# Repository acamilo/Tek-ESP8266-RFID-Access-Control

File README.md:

# Tek-ESP8266-RFID-Access-Control

## Requirements ##
* Accept [Wiegand](https://en.wikipedia.org/wiki/Wiegand_interface) data from a rfid reader
* Power everything off of a 12v wall wart.
* Query a database over WiFi with card data.
* Controll Relays, Lights, Door latches

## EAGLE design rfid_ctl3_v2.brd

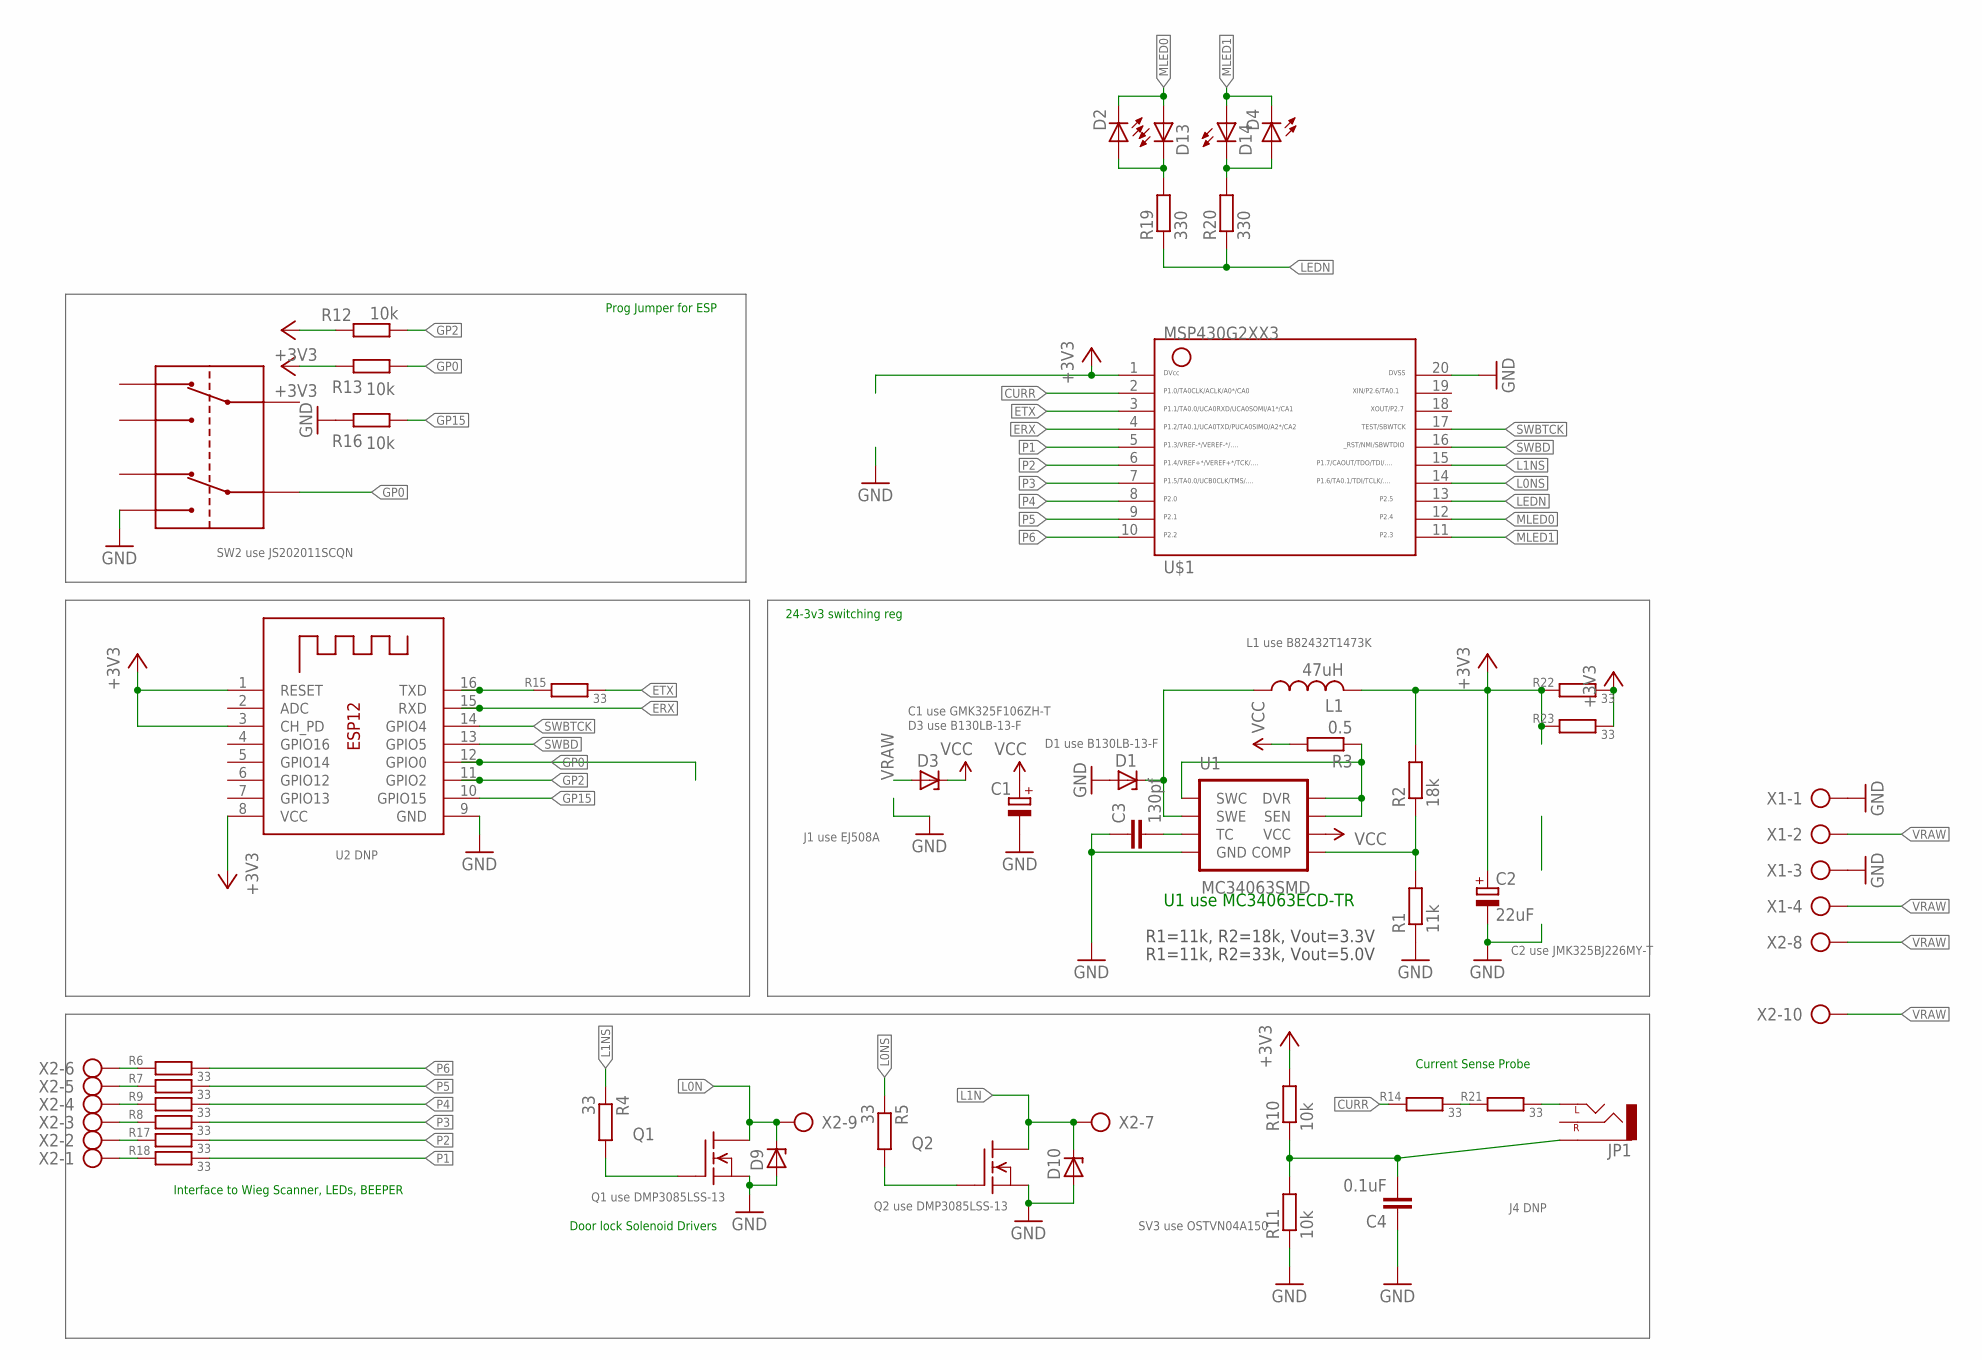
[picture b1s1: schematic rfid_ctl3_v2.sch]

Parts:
C1: CPOL-EUE2.5-7; E2,5-7
C2: 22uF; E2,5-7
C3: 130pf; C1206
C4: 0.1uF; C1206
D1, D3, D9, D10: ZENER-DIODESMB; SMB
D2, D4, D13, D14: LED5MM
JP1: AUDIO-JACKSMD2; AUDIO-JACK-3.5MM-SMD
L1: 47uH; L1812
Q1, Q2: FDS5680; SO-8
R1: 11k; R1206
R2: 18k; R1206
R3: 0.5; R1206
R4, R5, R6, R7, R8, R9, R14, R15, R17, R18, R21: 33; R1206
R10, R11, R12, R13, R16: 10k; R1206
R19, R20: 330; R1206
R22, R23: 33; R6332
SW2: L202011MS02Q; SMT
U1: MC34063SMD; SO08
U2: ESP-12
U$1: G2XX3---N20; N20
X1: AK300/4
X2: AK300/10

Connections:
+3V3: C2.+, L1.2, R2.2, R10.2, R12.2, R13.2, R22.1, R22.2, R23.1, R23.2, U2.1 (RESET), U2.3 (CH_PD), U2.8 (VCC), U$1.1
CURR: R14.1, U$1.2
ERX: U2.15 (RXD), U$1.4
ETX: R15.2, U$1.3
GND: C1.-, C2.-, C3.1, C4.1, D1.A, D9.A, D10.A, Q1.1 (S), Q1.2 (S), Q1.3 (S), Q2.1 (S), Q2.2 (S), Q2.3 (S), R1.1, R11.1, R16.2, SW2.B1, U1.4 (GND), U2.9 (GND), U$1.20, X1.1, X1.3
GP0: R13.1, SW2.B, U2.12 (GPIO0)
GP2: R12.1, U2.11 (GPIO2)
GP15: R16.1, U2.10 (GPIO15)
L0N: D9.C, Q1.5 (D), Q1.6 (D), Q1.7 (D), Q1.8 (D), X2.9
L0NS: R5.1, U$1.14
L1N: D10.C, Q2.5 (D), Q2.6 (D), Q2.7 (D), Q2.8 (D), X2.7
L1NS: R4.1, U$1.15
LEDN: R19.1, R20.1, U$1.13
MLED0: D2.K (C), D13.A, U$1.12
MLED1: D4.K (C), D14.A, U$1.11
unnamed: Q1.4 (G), R4.2
unnamed: C3.2, U1.3 (TC)
unnamed: D1.C, L1.1, U1.2 (SWE)
unnamed: Q2.4 (G), R5.2
unnamed: R1.2, R2.1, U1.5 (COMP)
unnamed: R3.1, U1.1 (SWC), U1.7 (SEN), U1.8 (DVR)
unnamed: R14.2, R21.1
unnamed: R6.1, X2.6
unnamed: R7.1, X2.5
unnamed: R8.1, X2.4
unnamed: R9.1, X2.3
unnamed: C4.2, JP1.SLEEVE, R10.1, R11.2
unnamed: JP1.TIP (LEFT), R21.2
unnamed: D2.A, D13.K (C), R19.2
unnamed: D4.A, D14.K (C), R20.2
unnamed: R17.1, X2.2
unnamed: R18.1, X2.1
unnamed: R15.1, U2.16 (TXD)
P1: R18.2, U$1.5
P2: R17.2, U$1.6
P3: R9.2, U$1.7
P4: R8.2, U$1.8
P5: R7.2, U$1.9
P6: R6.2, U$1.10
SWBD: U2.13 (GPIO5), U$1.16
SWBTCK: U2.14 (GPIO4), U$1.17
VCC: C1.+, D3.C, R3.2, U1.6 (VCC)
VRAW: D3.A, X1.2, X1.4, X2.8, X2.10

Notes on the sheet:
R1=11k, R2=18k, Vout=3.3V
R1=11k, R2=33k, Vout=5.0V
Q1 use DMP3085LSS-13
Q2 use DMP3085LSS-13
C2 use JMK325BJ226MY-T
C1 use GMK325F106ZH-T
D3 use B130LB-13-F
D1 use B130LB-13-F
L1 use B82432T1473K
J1 use EJ508A
SV3 use OSTVN04A150
SW2 use JS202011SCQN
J4 DNP
U2 DNP
U1 use MC34063ECD-TR
Prog Jumper for ESP
24-3v3 switching reg
Interface to Wieg Scanner, LEDs, BEEPER
Door lock Solenoid Drivers
Current Sense Probe

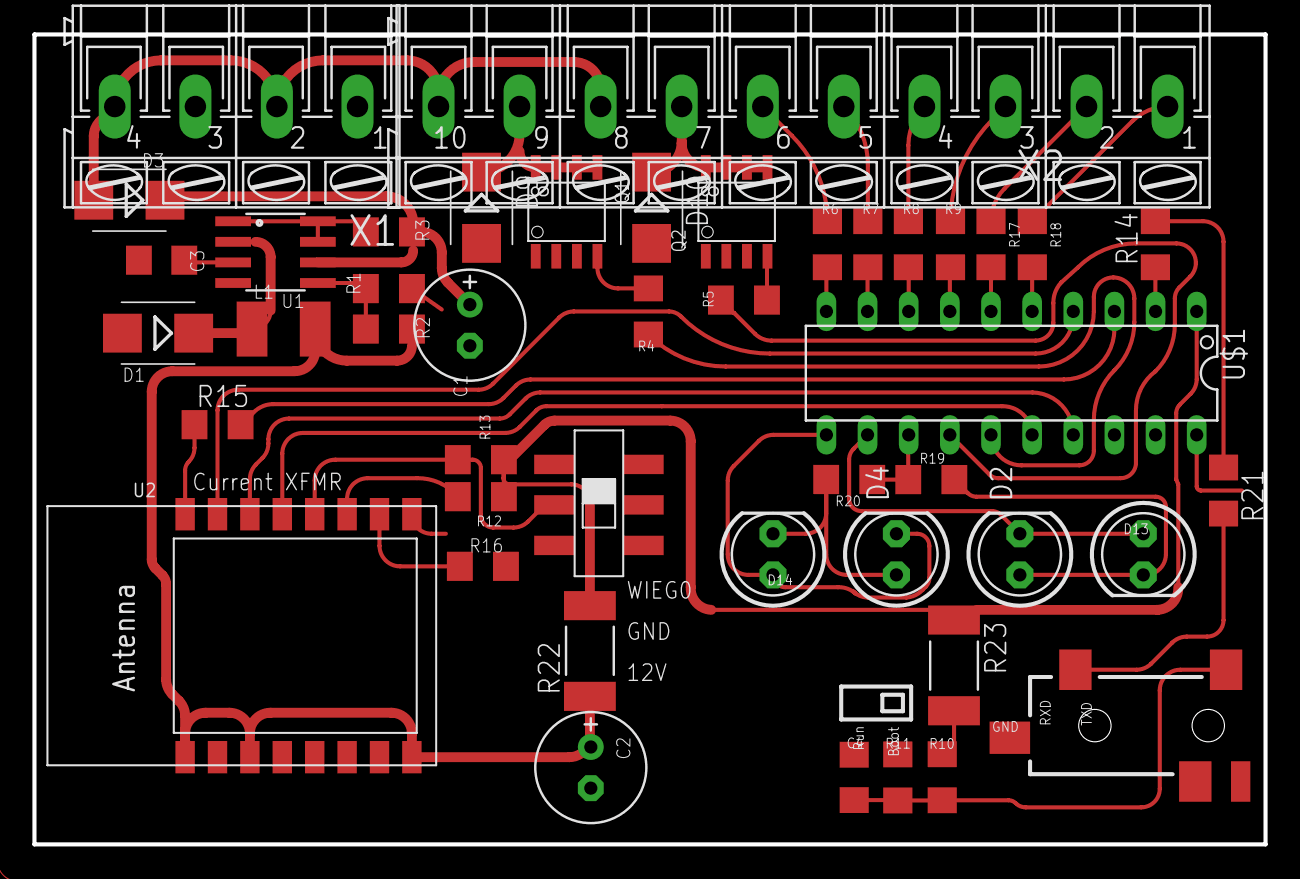
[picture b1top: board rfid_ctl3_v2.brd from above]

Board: 2 copper layers, 76.0 x 50.0 mm, 45 parts (0 on the bottom side), 43 nets.

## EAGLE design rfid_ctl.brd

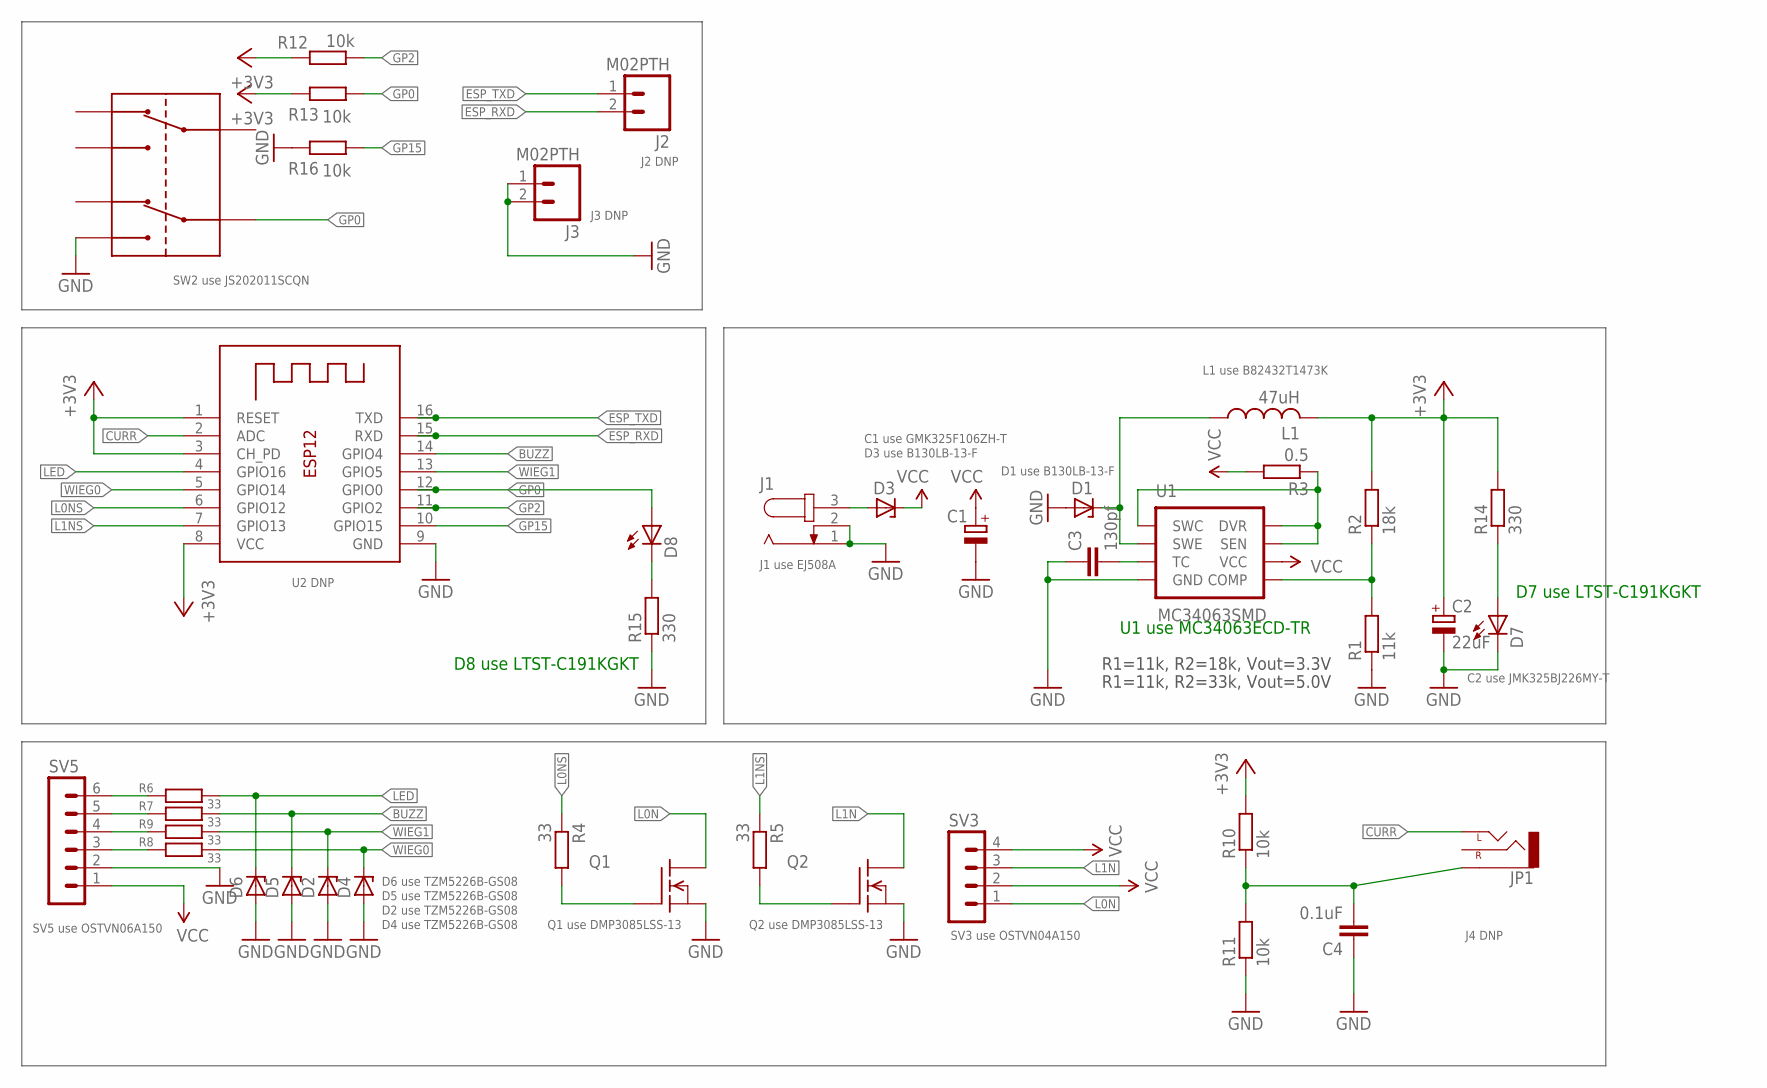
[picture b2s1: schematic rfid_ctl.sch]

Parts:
C1: CPOL-EUB/3528-21R; B/3528-21R
C2: 22uF; B/3528-21R
C3: 130pf; C0603
C4: 0.1uF; C0603
D1, D3: ZENER-DIODESMB; SMB
D2, D4, D5, D6: ZENER-DIODESOD80C; SOD80C
D7, D8: LEDCHIP-LED0603; CHIP-LED0603
J1: JACK-PLUG0; SPC4077
J2, J3: M02PTH; 1X02
JP1: AUDIO-JACKSMD2; AUDIO-JACK-3.5MM-SMD
L1: 47uH; L1812
Q1, Q2: FDS5680; SO-8
R1: 11k; R0603
R2: 18k; R0603
R3: 0.5; R0603
R4, R5, R6, R7, R8, R9: 33; R0603
R10, R11, R12, R13, R16: 10k; R0603
R14, R15: 330; R0603
SV3: MA04-1
SV5: MA06-1
SW2: L202011MS02Q; SMT
U1: MC34063SMD; SO08
U2: ESP-12

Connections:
+3V3: C2.+, L1.2, R2.2, R10.2, R12.2, R13.2, R14.2, U2.1 (RESET), U2.3 (CH_PD), U2.8 (VCC)
BUZZ: D5.C, R7.2, U2.14 (GPIO4)
CURR: JP1.TIP (LEFT), U2.2 (ADC)
ESP_RXD: J2.2, U2.15 (RXD)
ESP_TXD: J2.1, U2.16 (TXD)
GND: C1.-, C2.-, C3.1, C4.1, D1.A, D2.A, D4.A, D5.A, D6.A, D7.C, J1.1, J1.2, J3.1, J3.2, Q1.1 (S), Q1.2 (S), Q1.3 (S), Q2.1 (S), Q2.2 (S), Q2.3 (S), R1.1, R11.1, R15.1, R16.2, SV5.2, SW2.B1, U1.4 (GND), U2.9 (GND)
GP0: D8.A, R13.1, SW2.B, U2.12 (GPIO0)
GP2: R12.1, U2.11 (GPIO2)
GP15: R16.1, U2.10 (GPIO15)
L0N: Q1.5 (D), Q1.6 (D), Q1.7 (D), Q1.8 (D), SV3.1
L0NS: R4.1, U2.6 (GPIO12)
L1N: Q2.5 (D), Q2.6 (D), Q2.7 (D), Q2.8 (D), SV3.3
L1NS: R5.1, U2.7 (GPIO13)
LED: D6.C, R6.2, U2.4 (GPIO16)
unnamed: Q1.4 (G), R4.2
unnamed: C3.2, U1.3 (TC)
unnamed: D1.C, L1.1, U1.2 (SWE)
unnamed: Q2.4 (G), R5.2
unnamed: R1.2, R2.1, U1.5 (COMP)
unnamed: R3.1, U1.1 (SWC), U1.7 (SEN), U1.8 (DVR)
unnamed: D3.A, J1.3
unnamed: R6.1, SV5.6
unnamed: R7.1, SV5.5
unnamed: R8.1, SV5.4
unnamed: R9.1, SV5.3
unnamed: C4.2, JP1.SLEEVE, R10.1, R11.2
unnamed: D7.A, R14.1
unnamed: D8.C, R15.2
VCC: C1.+, D3.C, R3.2, SV3.2, SV3.4, SV5.1, U1.6 (VCC)
WIEG0: D4.C, R9.2, U2.5 (GPIO14)
WIEG1: D2.C, R8.2, U2.13 (GPIO5)

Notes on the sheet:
R1=11k, R2=18k, Vout=3.3V
R1=11k, R2=33k, Vout=5.0V
Q1 use DMP3085LSS-13
Q2 use DMP3085LSS-13
D6 use TZM5226B-GS08
D5 use TZM5226B-GS08
D2 use TZM5226B-GS08
D4 use TZM5226B-GS08
C2 use JMK325BJ226MY-T
C1 use GMK325F106ZH-T
D3 use B130LB-13-F
D1 use B130LB-13-F
L1 use B82432T1473K
J1 use EJ508A
SV5 use OSTVN06A150
SV3 use OSTVN04A150
SW2 use JS202011SCQN
J2 DNP
J3 DNP
J4 DNP
U2 DNP
U1 use MC34063ECD-TR
D7 use LTST-C191KGKT
D8 use LTST-C191KGKT

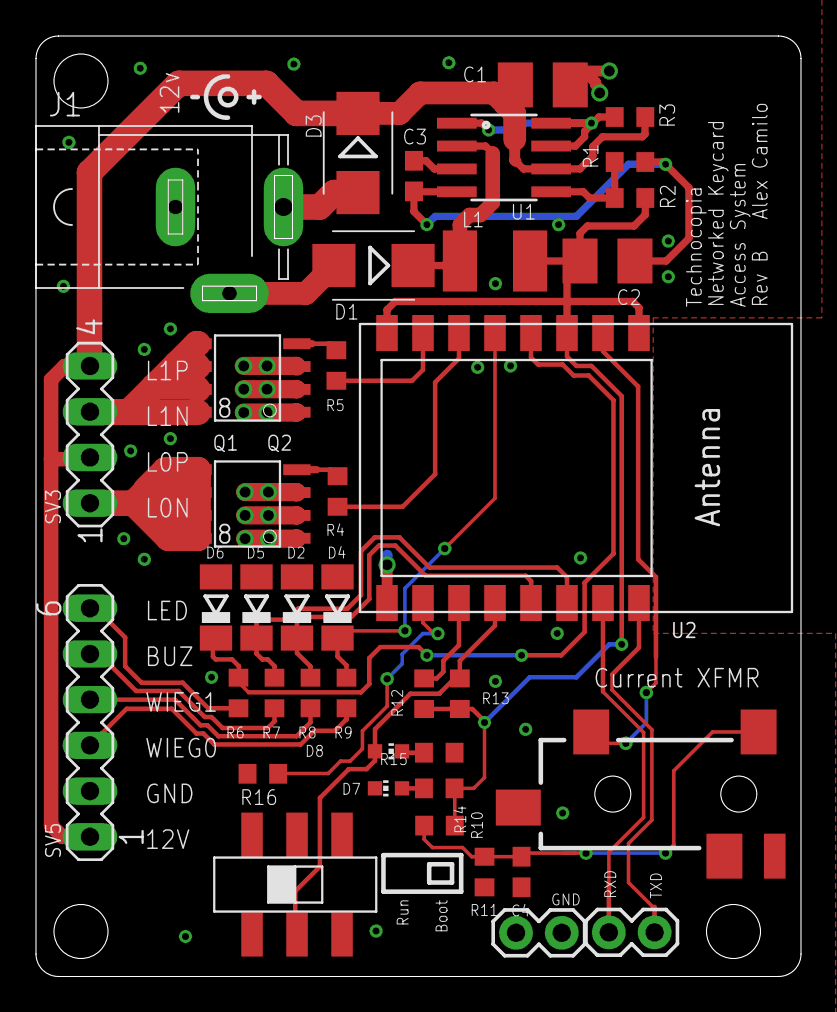
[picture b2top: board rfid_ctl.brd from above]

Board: 2 copper layers, 42.5 x 52.2 mm, 40 parts (0 on the bottom side), 31 nets.

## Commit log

2015-11-04 comitted rev A
2015-11-04 added board image from oshpark order
2015-11-04 Added Schematic IMG
2015-12-09 GPIO pulled low and HP jack swapped with something sourcable
2015-12-11 more cleanup
2016-05-02 Millable board pushed
2016-05-04 cleaned up schem and added schematic png
2016-05-04 Board image

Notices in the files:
parts and their libraries:
SparkFun-Connectors: Licensing: Creative Commons ShareAlike 4.0 International - https://creativecommons.org/licenses/by-sa/4.0
